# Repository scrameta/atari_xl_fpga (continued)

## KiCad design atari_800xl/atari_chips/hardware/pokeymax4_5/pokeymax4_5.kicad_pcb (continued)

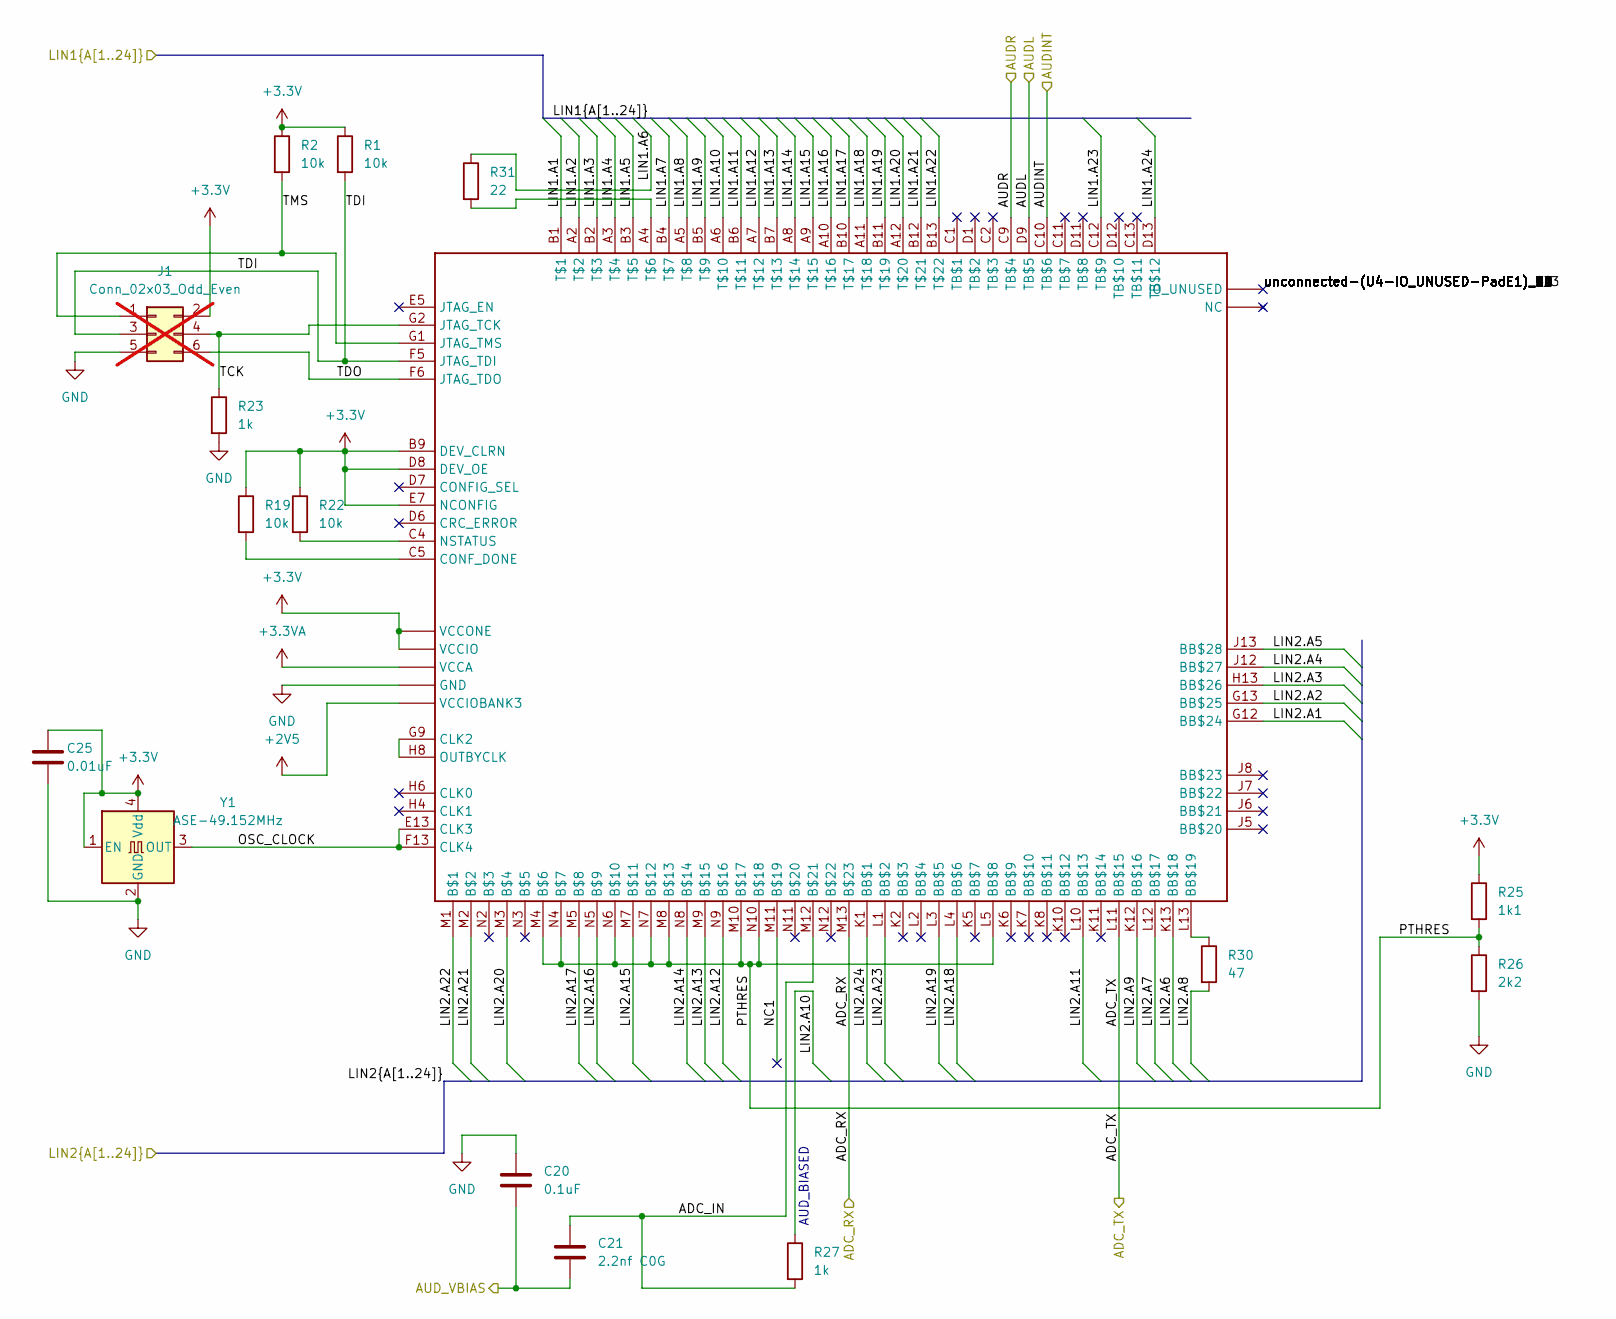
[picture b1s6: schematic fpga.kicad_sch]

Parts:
C20: 0.1uF; C_0402_1005Metric; LCSC C1525
C21: 2.2nf C0G; C_0402_1005Metric; LCSC C2987940
C25: 0.01uF; C_0603_1608Metric; LCSC C57112
J1: Conn_02x03_Odd_Even; PinHeader_2x03_P2.54mm_Vertical; not fitted
R1, R2, R19, R22: 10k; R_0603_1608Metric; LCSC C25804
R23: 1k; R_0603_1608Metric; LCSC C21190
R25: 1k1; R_0603_1608Metric; LCSC C705736
R26: 2k2; R_0603_1608Metric; LCSC C4190
R27: 1k; R_0402_1005Metric; LCSC C11702
R30: 47; R_0402_1005Metric; LCSC C137973
R31: 22; R_0402_1005Metric; LCSC C25092
U4: U169SMALL; LCSC C1551099
Y1: ASE-49.152MHz; Oscillator_SMD_Abracon_ASE-4Pin_3.2x2.5mm; LCSC C2901591

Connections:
+2V5: U4.L6 (VCCIOBANK3), U4.L7 (VCCIOBANK3), U4.L8 (VCCIOBANK3); also elsewhere on the board
+3.3V: C25.1, J1.2, R1.1, R2.1, R19.1, R22.1, R25.1, U4.B9 (DEV_CLRN), U4.C6 (VCCIO), U4.C7 (VCCIO), U4.C8 (VCCIO), U4.D8 (DEV_OE), U4.E7 (NCONFIG), U4.F2 (VCCIO), U4.F7 (VCCONE), U4.F11 (VCCIO), U4.G3 (VCCIO), U4.G6 (VCCONE), U4.G8 (VCCONE), U4.G11 (VCCIO), U4.H7 (VCCONE), U4.H11 (VCCIO), U4.J3 (VCCIO), U4.J11 (VCCIO), U4.K3 (VCCIO), Y1.1 (EN), Y1.4 (Vdd); also elsewhere on the board
+3.3VA: U4.D4 (VCCA), U4.D10 (VCCA), U4.K4 (VCCA), U4.K9 (VCCA); also elsewhere on the board
/ADC/ADC_RX: U4.M13; also elsewhere on the board
/ADC/ADC_TX: U4.L11 (BB$15); also elsewhere on the board
/ADC/AUD_VBIAS: C20.2, C21.2; also elsewhere on the board
/Audio output/AUDINT: U4.C10 (TB$6); also elsewhere on the board
/Audio output/AUDL: U4.D9 (TB$5); also elsewhere on the board
/Audio output/AUDR: U4.C9 (TB$4); also elsewhere on the board
/FPGA/ADC_IN: C21.1, R27.2, U4.M12
/FPGA/LIN1.A1: U4.B1; also elsewhere on the board
/FPGA/LIN1.A2: U4.A2; also elsewhere on the board
/FPGA/LIN1.A3: U4.B2; also elsewhere on the board
/FPGA/LIN1.A4: U4.A3; also elsewhere on the board
/FPGA/LIN1.A5: U4.B3; also elsewhere on the board
/FPGA/LIN1.A6: R31.1; also elsewhere on the board
/FPGA/LIN1.A7: U4.B4; also elsewhere on the board
/FPGA/LIN1.A8: U4.A5; also elsewhere on the board
/FPGA/LIN1.A9: U4.B5; also elsewhere on the board
/FPGA/LIN1.A10: U4.A6; also elsewhere on the board
/FPGA/LIN1.A11: U4.B6; also elsewhere on the board
/FPGA/LIN1.A12: U4.A7; also elsewhere on the board
/FPGA/LIN1.A13: U4.B7; also elsewhere on the board
/FPGA/LIN1.A14: U4.A8; also elsewhere on the board
/FPGA/LIN1.A15: U4.A9; also elsewhere on the board
/FPGA/LIN1.A16: U4.A10; also elsewhere on the board
/FPGA/LIN1.A17: U4.B10; also elsewhere on the board
/FPGA/LIN1.A18: U4.A11; also elsewhere on the board
/FPGA/LIN1.A19: U4.B11; also elsewhere on the board
/FPGA/LIN1.A20: U4.A12; also elsewhere on the board
/FPGA/LIN1.A21: U4.B12; also elsewhere on the board
/FPGA/LIN1.A22: U4.B13; also elsewhere on the board
/FPGA/LIN1.A23: U4.C12 (TB$9); also elsewhere on the board
/FPGA/LIN1.A24: U4.D13 (TB$12); also elsewhere on the board
/FPGA/LIN2.A1: U4.G12 (BB$24); also elsewhere on the board
/FPGA/LIN2.A2: U4.G13 (BB$25); also elsewhere on the board
/FPGA/LIN2.A3: U4.H13 (BB$26); also elsewhere on the board
/FPGA/LIN2.A4: U4.J12 (BB$27); also elsewhere on the board
/FPGA/LIN2.A5: U4.J13 (BB$28); also elsewhere on the board
/FPGA/LIN2.A6: U4.K13 (BB$18); also elsewhere on the board
/FPGA/LIN2.A7: U4.L12 (BB$17); also elsewhere on the board
/FPGA/LIN2.A8: R30.2; also elsewhere on the board
/FPGA/LIN2.A9: U4.K12 (BB$16); also elsewhere on the board
/FPGA/LIN2.A10: R27.1; also elsewhere on the board
/FPGA/LIN2.A11: U4.L10 (BB$13); also elsewhere on the board
/FPGA/LIN2.A12: U4.N9; also elsewhere on the board
/FPGA/LIN2.A13: U4.M9; also elsewhere on the board
/FPGA/LIN2.A14: U4.N8; also elsewhere on the board
/FPGA/LIN2.A15: U4.M7; also elsewhere on the board
/FPGA/LIN2.A16: U4.N5; also elsewhere on the board
/FPGA/LIN2.A17: U4.M5; also elsewhere on the board
/FPGA/LIN2.A18: U4.L4 (BB$6); also elsewhere on the board
/FPGA/LIN2.A19: U4.L3 (BB$5); also elsewhere on the board
/FPGA/LIN2.A20: U4.M3; also elsewhere on the board
/FPGA/LIN2.A21: U4.M2; also elsewhere on the board
/FPGA/LIN2.A22: U4.M1; also elsewhere on the board
/FPGA/LIN2.A23: U4.L1 (BB$2); also elsewhere on the board
/FPGA/LIN2.A24: U4.K1 (BB$1); also elsewhere on the board
/FPGA/NC1: U4.M11
/FPGA/OSC_CLOCK: U4.E13 (CLK3), U4.F13 (CLK4), Y1.3 (OUT)
/FPGA/PTHRES: R25.2, R26.1, U4.L5 (BB$8), U4.M4, U4.M8, U4.M10, U4.N4, U4.N6, U4.N7, U4.N10
/FPGA/TCK: J1.4, R23.1, U4.G2 (JTAG_TCK)
/FPGA/TDI: J1.3, R1.2, U4.F5 (JTAG_TDI)
/FPGA/TDO: J1.6, U4.F6 (JTAG_TDO)
/FPGA/TMS: J1.1, R2.2, U4.G1 (JTAG_TMS)
GND: C20.1, C25.2, J1.5, R23.2, R26.2, U4.A1 (GND), U4.A13 (GND), U4.B8 (GND), U4.C3 (GND), U4.D5 (GND), U4.E11 (GND), U4.F3 (GND), U4.G7 (GND), U4.H12 (GND), U4.J4 (GND), U4.L9 (GND), U4.M6 (GND), U4.N1 (GND), U4.N13 (GND), Y1.2 (GND); also elsewhere on the board
unnamed: R30.1, U4.L13 (BB$19)
unnamed: U4.G9 (CLK2), U4.H8 (OUTBYCLK)
unnamed: R19.2, U4.C5 (CONF_DONE)
unnamed: R22.2, U4.C4 (NSTATUS)
unnamed: R31.2, U4.A4

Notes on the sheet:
AUD_BIASED

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
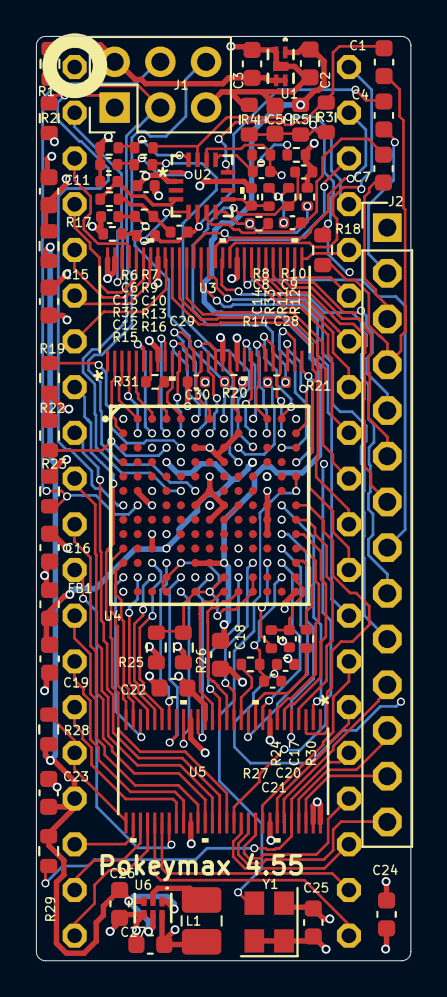
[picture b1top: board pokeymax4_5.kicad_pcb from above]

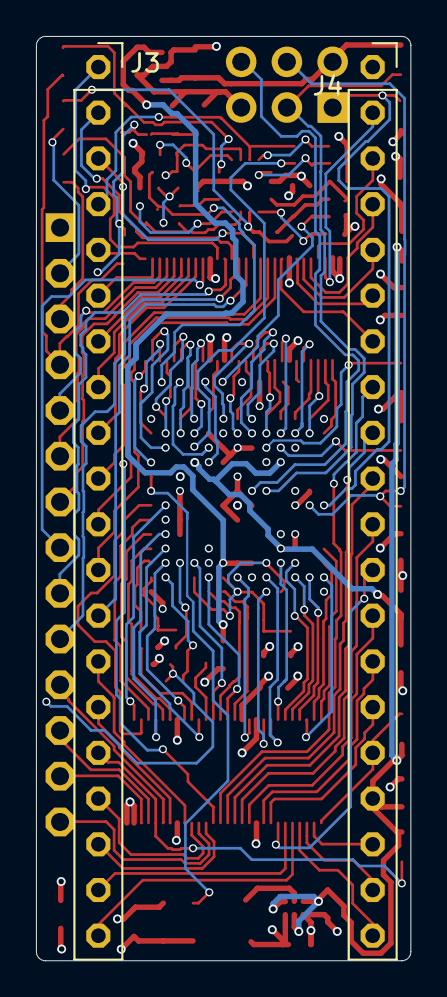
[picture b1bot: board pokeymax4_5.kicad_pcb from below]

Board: 4 copper layers, 20.8 x 51.3 mm, 76 parts (2 on the bottom side), 139 nets.

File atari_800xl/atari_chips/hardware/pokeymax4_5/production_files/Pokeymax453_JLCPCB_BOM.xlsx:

Designator | Footprint | JLCPCB Part #（optional） | Comment | Description | Mfgr part
C10,C20 | C_0402_1005Metric | C1525 | CAP CER 0.1UF 16V X7R 0402 | 100nF 16V X7R ±10% 0402 Multilayer Ceramic Capacitors MLCC - SMD/SMT ROHS | CL05B104KO5NNNC
R11,R9,R13 | R_0402_1005Metric | C278600 | RES SMD 560 OHM 1% 1/10W 0402 | -55℃~+155℃ 100mW 560Ω Thick Film Resistor ±1% ±100ppm/℃ 0402 Chip Resistor - Su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 | ERJ2RKF5600X
R18 | R_0603_1608Metric | C123420 | RES 220K OHM 1% 0603 | -55℃~+155℃ 100mW 220kΩ 75V Thick Film Resistor ±1% ±100ppm/℃ 0603 Chip Resistor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 | RC0603FR-07220KL
L1 | L_1008_2520Metric_Pad1.43x2.20mm_HandSolder | C171753 | FIXED IND 1UH 1.5A 113 MOHM SMD | 1.5A 112.5mΩ 1uH 70MHz ±20% 1008 Inductors (SMD) ROHS | LQM2HPN1R0MJ0L
R21,R20 | R_0402_1005Metric | C138002 | RES 33 OHM 1% 0402 | -55℃~+155℃ 33Ω 50V 62.5mW Thick Film Resistor ±1% ±100ppm/℃ 0402 Chip Resistor 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 | RC0402FR-0733RL
C7,C1,C4,C26 | C_0603_1608Metric | C415535 | CAP CER 2.2UF 25V X7R 0603 audio | 2.2uF 25V X7R ±10% 0603 Multilayer Ceramic Capacitors MLCC - SMD/SMT ROHS | GRM188Z71E225KE43D
C27 | C_0603_1608Metric | C1705 | CAP CER 4.7UF 10V X5R 0603 | 10V 4.7uF X5R ±10% 0603 Multilayer Ceramic Capacitors MLCC - SMD/SMT ROHS | CL10A475KP8NNNC
C24,C22,C18,C15,C3,C19,C2,C16,C23 | C_0603_1608Metric | C108079 | CAP CER 0.1UF 16V X7R 0603 | 100nF 16V X7R ±10% 0603 Multilayer Ceramic Capacitors MLCC - SMD/SMT ROHS | CC0603KRX7R7BB104
U2 | QFN16_3X3_STM | C2058240 | IC OPAMP GP 4 CIRCUIT 16QFN | -40℃~+125℃ 1.3MHz 120uA 1uV/℃ 2.3V~5.5V 20nV/√Hz@10kHz 21mA 27nA 4 4mV 5.5V 500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 | TSV854IQ4T
C11 | C_0603_1608Metric | C2762594 | CAP CER 22uF 16V 0603 | 16V 22uF X5R ±20% 0603 Multilayer Ceramic Capacitors MLCC - SMD/SMT ROHS | CL10A226MO7JZNC
R12,R15,R6 | R_0402_1005Metric | C490819 | RES SMD 20K OHM 0.1% 1/16W 0402 | -55℃~+155℃ 20kΩ 50V 63mW Thin Film Resistor ±0.1% ±25ppm/℃ 0402 Chip Resistor -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 | ERA2AEB203X
R26 | R_0603_1608Metric | C114662 | RES 2.2K OHM 1% 1/10W 0603 | -55℃~+155℃ 100mW 2.2kΩ 75V Thick Film Resistor ±1% ±100ppm/℃ 0603 Chip Resistor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 | RC0603FR-072K2L
Y1 | Oscillator_SMD_Abracon_ASE-4Pin_3.2x2.5mm | C2901591 | RES 2.2K OHM 1% 1/10W 0603 | -40℃~+85℃ 1.62V~3.63V 20mA 49.152MHz CMOS ±20ppm ±30ppm SMD3225-4P Crystal Osci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 | SX3M49.152M20F30TNN
FB1 | L_0603_1608Metric | C710367 | FERRITE BEAD 600 OHM 0603 1LN | -55℃~+125℃ 1 350mΩ 500mA 600Ω@100MHz ±25% 0603 Ferrite Beads ROHS | BLM18EG601SZ1D
C14,C13,C8 | C_0402_1005Metric | C882581 | CAP CER 220pF C0G 0402 | 220pF 50V C0G ±1% 0402 Multilayer Ceramic Capacitors MLCC - SMD/SMT ROHS | GCM1555C1H221FA16D
U5,U3 | DGV56-L | C2674751 | IC BUS SWITCH 12 X 1:1 56-TVSOP | -40℃~+85℃ 0.25ns@3.3V,50pF 2.3V~3.6V 24/24 70uA Single Supply TVSOP-56 Signal S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 | SN74CB3T16211DGVR
C17 | C_0402_1005Metric | C161523 | CAP CER 1000PF 50V C0G/NP0 0403 | 1nF 50V C0G ±1% 0402 Multilayer Ceramic Capacitors MLCC - SMD/SMT ROHS | GRM1555C1H102FA01D
R5 | R_0603_1608Metric | C25805 | RES 110K OHM 1% 1/10W 0603 | -55℃~+155℃ 100mW 110kΩ 75V Thick Film Resistor ±1% ±100ppm/℃ 0603 Chip Resistor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 | 0603WAF1103T5E
R1,R2,R22,R19,R4 | R_0603_1608Metric | C130232 | RES 10K OHM 1% 1/10W 0603 | -55℃~+155℃ 100mW 10kΩ 75V Thick Film Resistor ±1% ±100ppm/℃ 0603 Chip Resistor 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 | RK73H1JTTD1002F
R17 | R_0603_1608Metric | C109318 | RES 10 OHM 1% 1/10W 0603 | -55℃~+155℃ 100mW 10Ω 75V Thick Film Resistor ±1% ±200ppm/℃ 0603 Chip Resistor -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 | RC0603FR-0710RL
R24 | R_0402_1005Metric | C138041 | RES 1k1 OHM 1% 0402 | -55℃~+155℃ 1.1kΩ 50V 62.5mW Thick Film Resistor ±1% ±100ppm/℃ 0402 Chip Resisto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 | RC0402FR-071K1L
C9,C6,C12 | C_0402_1005Metric | C576740 | CAP 18nF 0402 audio | 18nF 50V X7R ±10% 0402 Multilayer Ceramic Capacitors MLCC - SMD/SMT ROHS | CC0402KRX7R9BB183
U1 | TDFN4_1P2X1P6_MCH | C622555 | IC REG LINEAR 2.5V 200MA 4-TMLF | -40℃~+125℃@(Tj) 1 2.5V 200mA 3.6V 85dB@(100Hz) Fixed Over Current Protection Po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 | MIC94310-JYMT-TR
R14,R7,R16,R10 | R_0402_1005Metric | C25744 | RES SMD 10K OHM 0.1% 1/16W 0402 | -55℃~+155℃ 10kΩ 50V 62.5mW Thick Film Resistor ±1% ±100ppm/℃ 0402 Chip Resistor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 | 0402WGF1002TCE
R3 | R_0603_1608Metric | C105579 | RES 47K OHM 0603 | -55℃~+155℃ 100mW 47kΩ 75V Thick Film Resistor ±1% ±100ppm/℃ 0603 Chip Resistor 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 | RC0603FR-0747KL
R8 | R_0402_1005Metric | C166559 | RES 50K OHM 1% 1/16W 0402 | -55℃~+155℃ 50V 50kΩ 62.5mW Thick Film Resistor ±1% ±100ppm/℃ 0402 Chip Resistor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 | RTT025002FTH
U6 | DRY6 | C398923 | IC REG BUCK 3.3V 500MA 6SON | -40℃~+125℃@(TJ) 1 2.05V~6V 22uA 2MHz 3.3V 500mA Buck Buck Built-In Fixed Yes SO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 | TPS62237DRYR
C21 | C_0402_1005Metric | C2987940 | CAP 2.2nF 0402 C0G | 2.2nF 50V C0G ±2% 0402 Multilayer Ceramic Capacitors MLCC - SMD/SMT ROHS | GRM1555C1H222GA01D
C5 | C_0603_1608Metric | C2959727 | CAP CER 10UF 10V X7R 0603 | 10V 10uF X7R ±10% 0603 Multilayer Ceramic Capacitors MLCC - SMD/SMT ROHS | GRM188Z71A106KA73D
R23 | R_0603_1608Metric | C2484712 | RES 1K OHM 1% 1/10W 0603 | -55℃~+155℃ 100mW 1kΩ 75V Thick Film Resistor ±1% ±100ppm/℃ 0603 Chip Resistor -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 | RMCF0603FT1K00
C25 | C_0603_1608Metric | C1589 | CAP CER 10000PF 50V X7R 0603 | 10nF 50V X7R ±10% 0603 Multilayer Ceramic Capacitors MLCC - SMD/SMT ROHS | CL10B103KB8NNNC
U4 | U169SMALL | C1551099 | IC FPGA 130 I/O 169UBGA | -40℃~+100℃ 1000 16000 562176bit UBGA-169 Programmable Logic Device (CPLDs/FPGAs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 | 10M16SCU169I7G
R25 | R_0603_1608Metric | C22764 | RES 1.1K OHM 1% 1/10W 0603 | -55℃~+155℃ 1.1kΩ 100mW 75V Thick Film Resistor ±1% ±100ppm/℃ 0603 Chip Resistor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 | 0603WAF1101T5E
R27 | R_0402_1005Metric | C106235 | RES 1K OHM 1% 0402 | -55℃~+155℃ 1kΩ 50V 62.5mW Thick Film Resistor ±1% ±100ppm/℃ 0402 Chip Resistor 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 | RC0402FR-071KL
R30 | R_0402_1005Metric | C25118 | RES 47 OHM 1% 0402 | -55℃~+155℃ 47Ω 50V 62.5mW Thick Film Resistor ±1% ±100ppm/℃ 0402 Chip Resistor 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 | 0402WGF470JTCE
R31 | R_0402_1005Metric | C25092 | RES 22 OHM 1% 0402 | -55℃~+155℃ 22Ω 50V 62.5mW Thick Film Resistor ±1% ±100ppm/℃ 0402 Chip Resistor 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 | 0402WGF220JTCE

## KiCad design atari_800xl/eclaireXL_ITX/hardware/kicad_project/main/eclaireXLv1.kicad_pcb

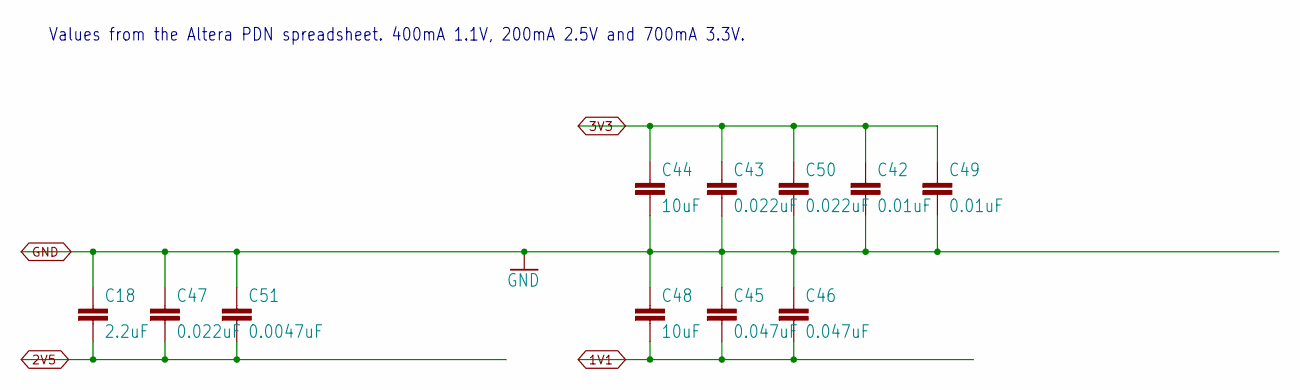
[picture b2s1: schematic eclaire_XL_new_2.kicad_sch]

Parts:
C18: 2.2uF; C0805
C42, C49: 0.01uF; C0805
C43, C47, C50: 0.022uF; C0805
C44, C48: 10uF; C0805
C45, C46: 0.047uF; C0805
C51: 0.0047uF; C0805

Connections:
1V1: C45.2, C46.2, C48.2; also elsewhere on the board
2V5: C18.2, C47.2, C51.2; also elsewhere on the board
3V3: C42.1, C43.1, C44.1, C49.1, C50.1; also elsewhere on the board

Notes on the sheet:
Values from the Altera PDN spreadsheet. 400mA 1.1V, 200mA 2.5V and 700mA 3.3V.

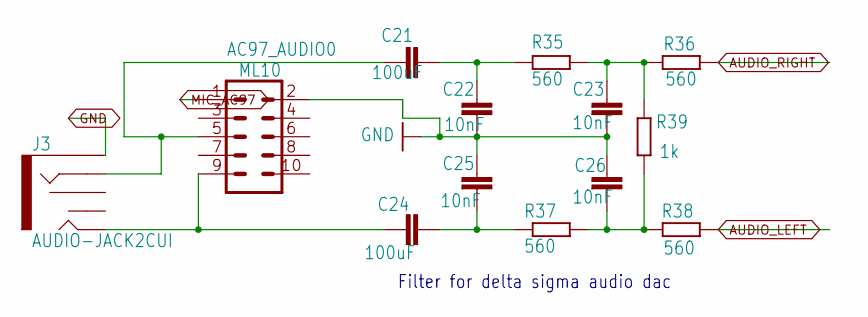
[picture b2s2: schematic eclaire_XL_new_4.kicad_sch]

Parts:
AC97_AUDIO0: ML10
C21, C24: 100uF; C1206
C22, C23, C25, C26: 10nF; C0805
J3: AUDIO-JACK2CUI; AUDIO-JACK-CUI-353X
R35, R36, R37, R38: 560; M0805
R39: 1k; M0805

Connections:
AUDIO_LEFT: R38.2; also elsewhere on the board
AUDIO_RIGHT: R36.2; also elsewhere on the board
MIC_AC97: AC97_AUDIO0.1; also elsewhere on the board
unnamed: C21.2, C22.1, R35.1
unnamed: C23.1, R35.2, R36.1, R39.2
unnamed: C26.2, R37.2, R38.1, R39.1
unnamed: AC97_AUDIO0.9, C24.1, J3.P$2 (TIP)
unnamed: AC97_AUDIO0.5, C21.1, J3.P$3 (RING)
unnamed: C24.2, C25.2, R37.1

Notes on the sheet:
Filter for delta sigma audio dac

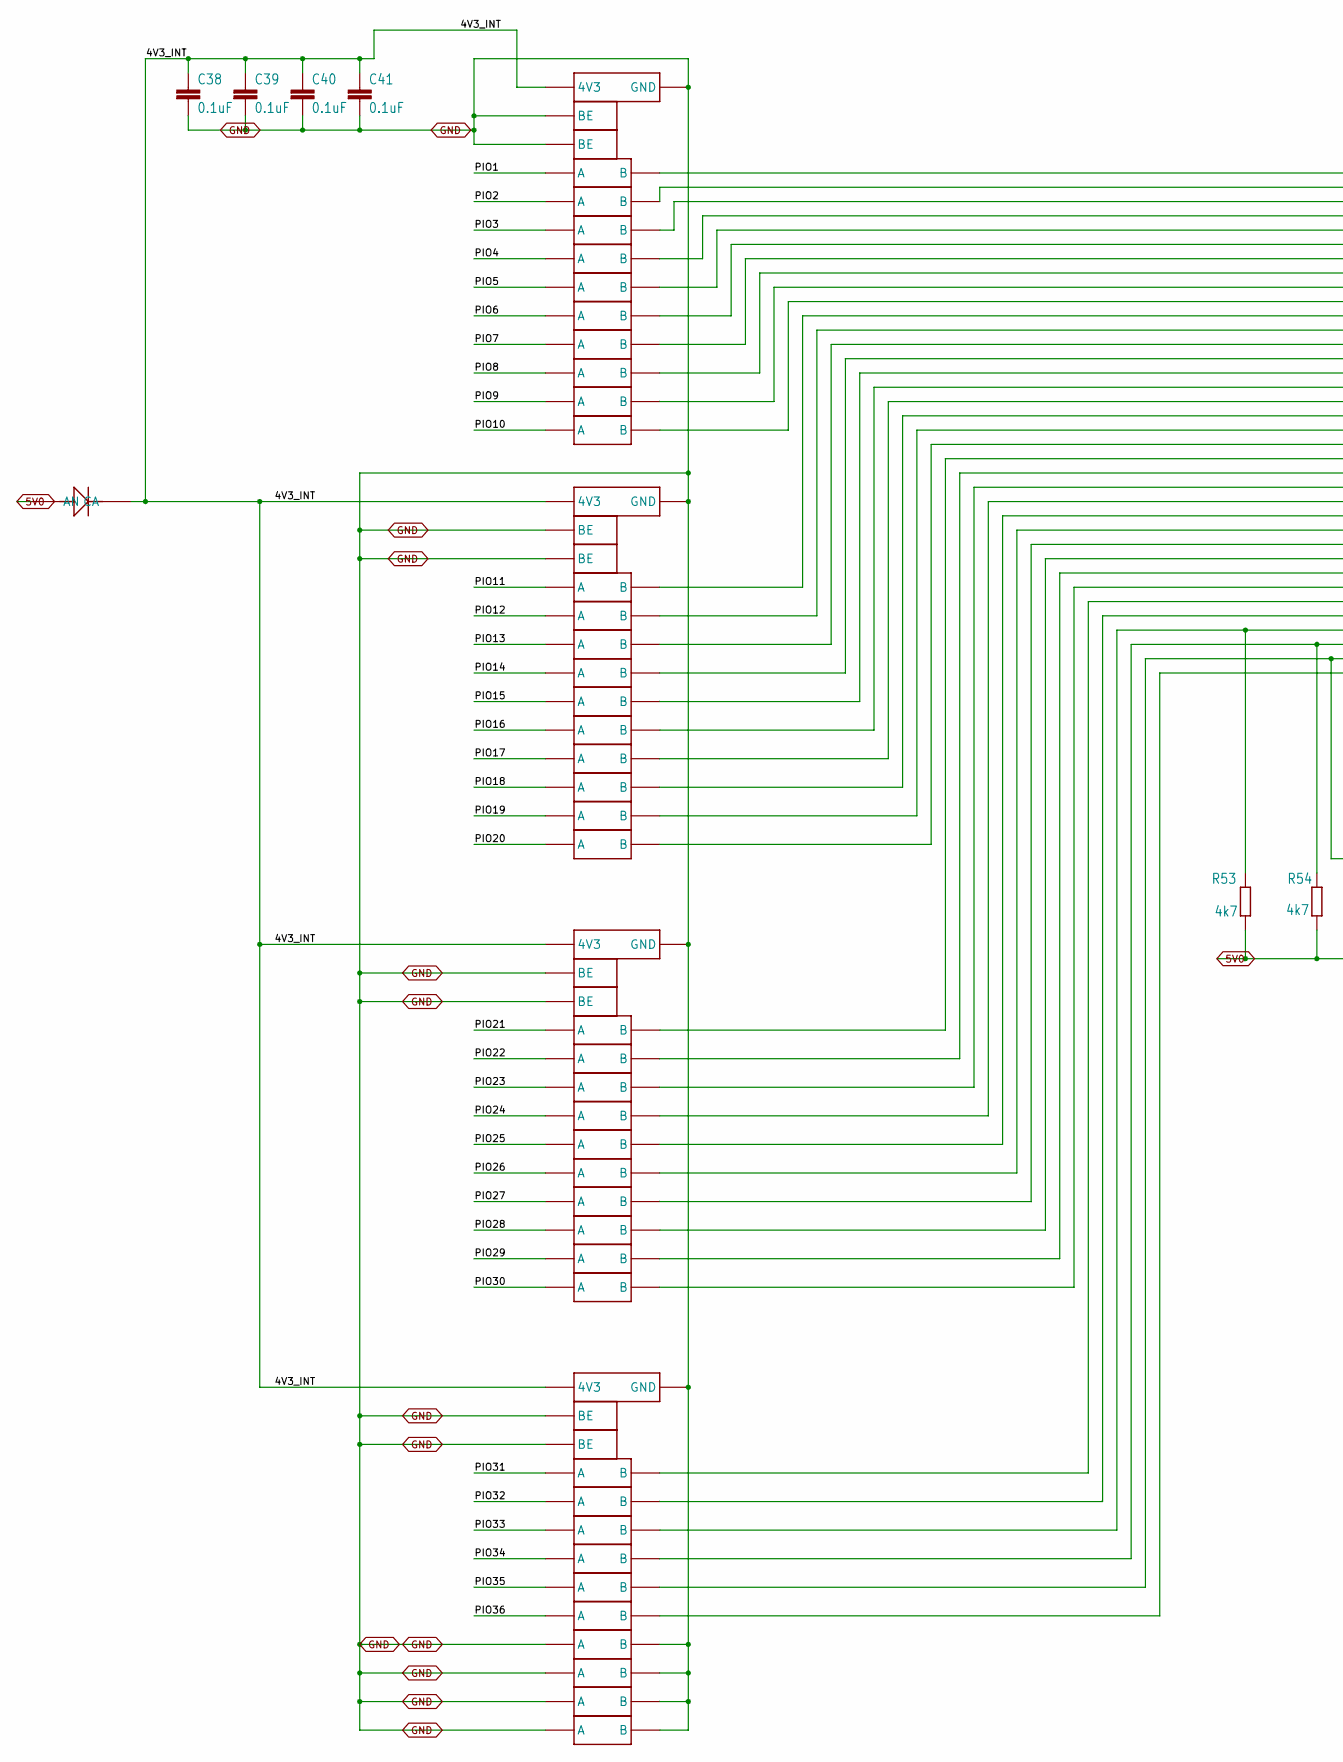
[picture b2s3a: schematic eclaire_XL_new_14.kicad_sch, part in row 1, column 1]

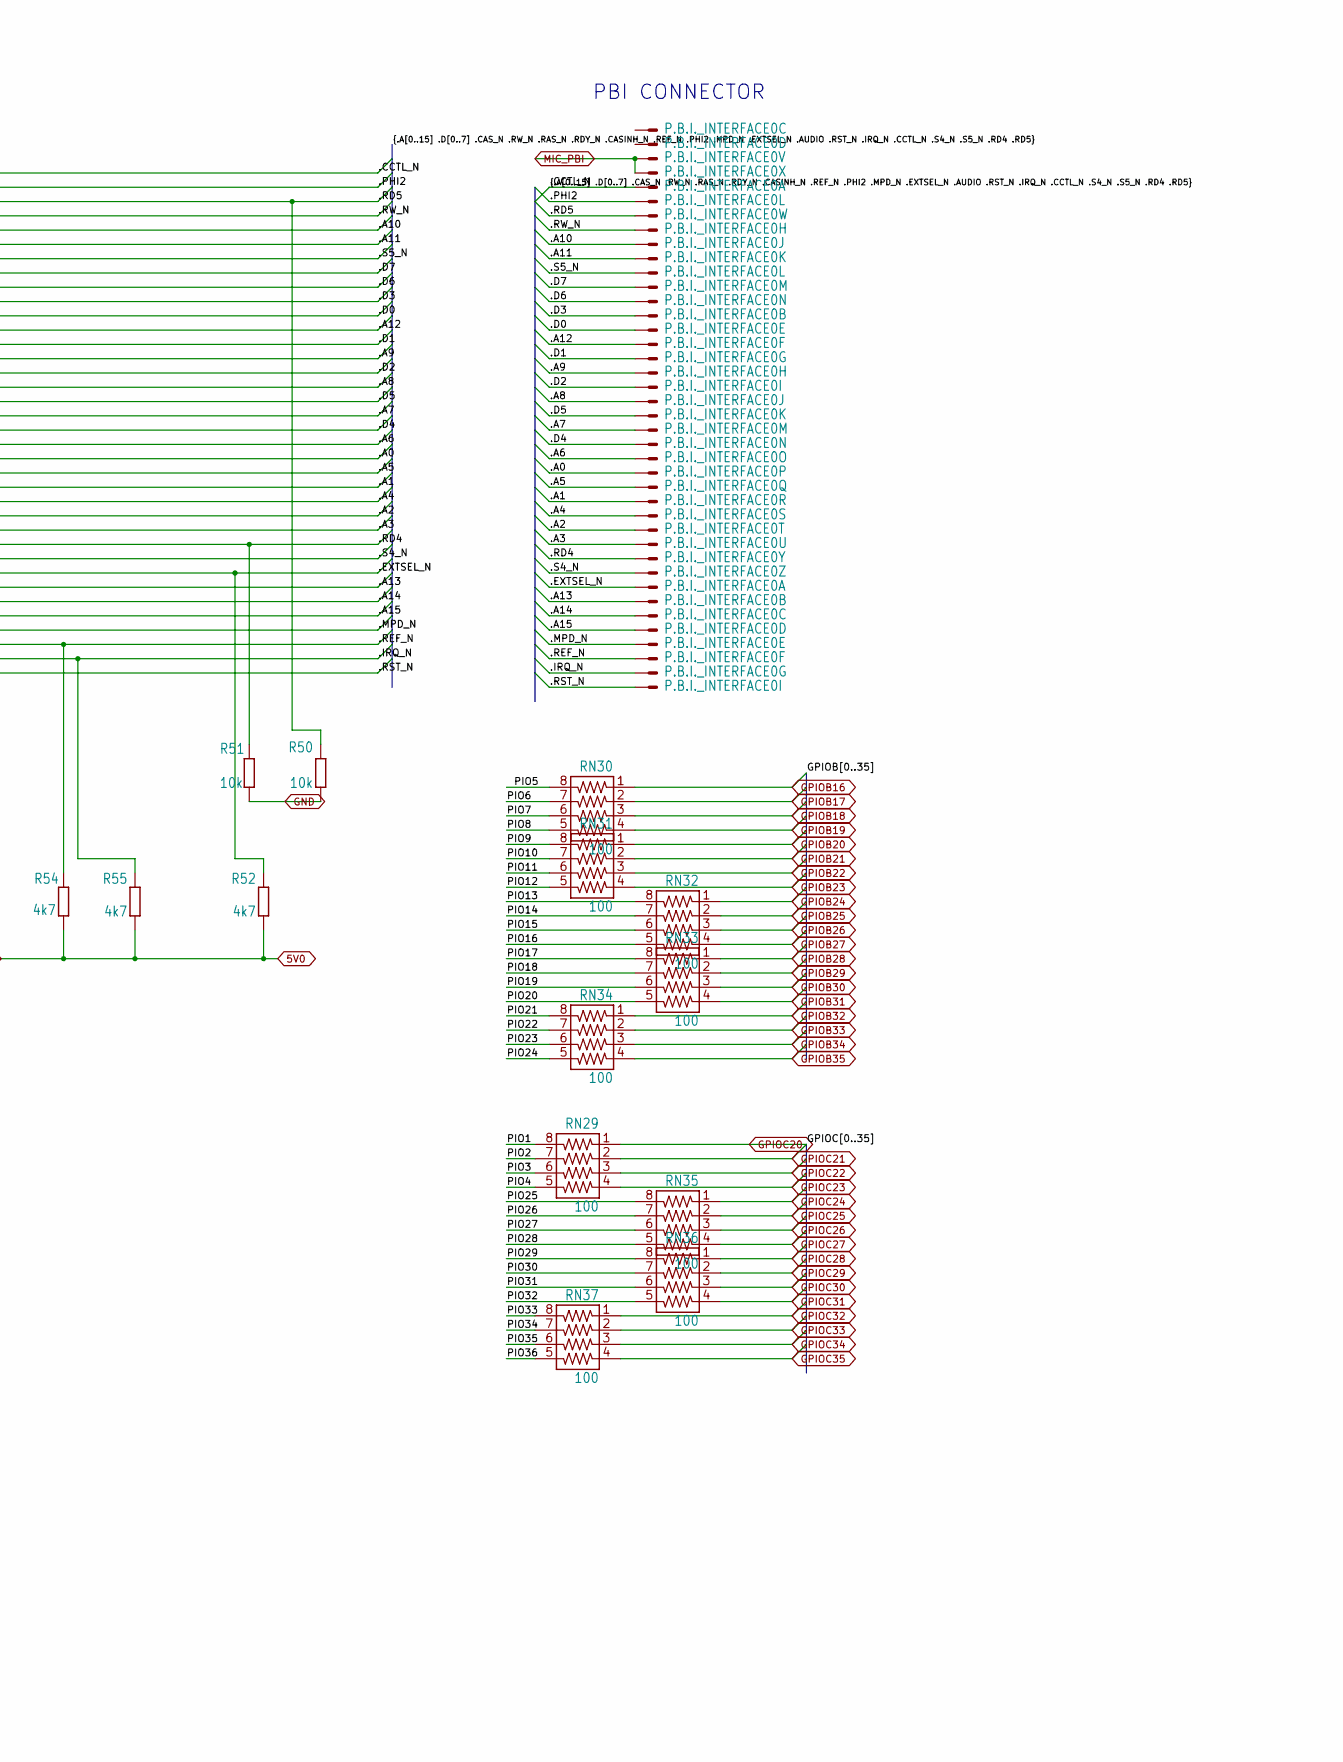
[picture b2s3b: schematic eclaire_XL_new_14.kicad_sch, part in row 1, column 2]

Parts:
C38, C39, C40, C41: 0.1uF; C0805K
D3: 1N4148; SOD123
IC1: U14; TSSOP24
IC2: U15; TSSOP24
IC3: U16; TSSOP24
IC4: U17; TSSOP24
P.B.I._INTERFACE0: ML40E; ML40
R50, R51: 10k; M0805
R52, R53, R54, R55: 4k7; M0805
RN29, RN30, RN31, RN32, RN33, RN34, RN35, RN36, RN37: 100; 743-8

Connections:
4V3_INT: C38.1, C39.1, C40.1, C41.1, D3.1 (CA), IC1.24 (4V3), IC2.24 (4V3), IC3.24 (4V3), IC4.24 (4V3)
5V0: D3.2 (AN), R52.1, R53.1, R54.1, R55.1; also elsewhere on the board
.A0: IC3.2 (B), P.B.I._INTERFACE0.23
.A1: IC3.6 (B), P.B.I._INTERFACE0.25
.A2: IC3.10 (B), P.B.I._INTERFACE0.27
.A3: IC3.15 (B), P.B.I._INTERFACE0.28
.A4: IC3.9 (B), P.B.I._INTERFACE0.26
.A5: IC3.5 (B), P.B.I._INTERFACE0.24
.A6: IC2.23 (B), P.B.I._INTERFACE0.22
.A7: IC2.19 (B), P.B.I._INTERFACE0.20
.A8: IC2.15 (B), P.B.I._INTERFACE0.18
.A9: IC2.9 (B), P.B.I._INTERFACE0.16
.A10: IC1.10 (B), P.B.I._INTERFACE0.5
.A11: IC1.15 (B), P.B.I._INTERFACE0.6
.A12: IC2.5 (B), P.B.I._INTERFACE0.14
.A13: IC3.23 (B), P.B.I._INTERFACE0.34
.A14: IC4.2 (B), P.B.I._INTERFACE0.35
.A15: IC4.5 (B), P.B.I._INTERFACE0.36
.CCTL_N: IC1.2 (B), P.B.I._INTERFACE0.1
.D0: IC2.2 (B), P.B.I._INTERFACE0.13
.D1: IC2.6 (B), P.B.I._INTERFACE0.15
.D2: IC2.10 (B), P.B.I._INTERFACE0.17
.D3: IC1.23 (B), P.B.I._INTERFACE0.10
.D4: IC2.20 (B), P.B.I._INTERFACE0.21
.D5: IC2.16 (B), P.B.I._INTERFACE0.19
.D6: IC1.20 (B), P.B.I._INTERFACE0.9
.D7: IC1.19 (B), P.B.I._INTERFACE0.8
.EXTSEL_N: IC3.20 (B), P.B.I._INTERFACE0.33, R52.2
.IRQ_N: IC4.10 (B), P.B.I._INTERFACE0.39, R55.2
.MPD_N: IC4.6 (B), P.B.I._INTERFACE0.37, R53.2
.PHI2: IC1.5 (B), P.B.I._INTERFACE0.2
.RD4: IC3.16 (B), P.B.I._INTERFACE0.31, R51.2
.RD5: IC1.6 (B), P.B.I._INTERFACE0.3, R50.2
.REF_N: IC4.9 (B), P.B.I._INTERFACE0.38, R54.2
.RST_N: IC4.15 (B), P.B.I._INTERFACE0.40
.RW_N: IC1.9 (B), P.B.I._INTERFACE0.4
.S4_N: IC3.19 (B), P.B.I._INTERFACE0.32
.S5_N: IC1.16 (B), P.B.I._INTERFACE0.7
GPIOB16: RN30.1; also elsewhere on the board
GPIOB17: RN30.2; also elsewhere on the board
GPIOB18: RN30.3; also elsewhere on the board
GPIOB19: RN30.4; also elsewhere on the board
GPIOB20: RN31.1; also elsewhere on the board
GPIOB21: RN31.2; also elsewhere on the board
GPIOB22: RN31.3; also elsewhere on the board
GPIOB23: RN31.4; also elsewhere on the board
GPIOB24: RN32.1; also elsewhere on the board
GPIOB25: RN32.2; also elsewhere on the board
GPIOB26: RN32.3; also elsewhere on the board
GPIOB27: RN32.4; also elsewhere on the board
GPIOB28: RN33.1; also elsewhere on the board
GPIOB29: RN33.2; also elsewhere on the board
GPIOB30: RN33.3; also elsewhere on the board
GPIOB31: RN33.4; also elsewhere on the board
GPIOB32: RN34.1; also elsewhere on the board
GPIOB33: RN34.2; also elsewhere on the board
GPIOB34: RN34.3; also elsewhere on the board
GPIOB35: RN34.4; also elsewhere on the board
GPIOC20: RN29.1; also elsewhere on the board
GPIOC21: RN29.2; also elsewhere on the board
GPIOC22: RN29.3; also elsewhere on the board
GPIOC23: RN29.4; also elsewhere on the board
GPIOC24: RN35.1; also elsewhere on the board
GPIOC25: RN35.2; also elsewhere on the board
GPIOC26: RN35.3; also elsewhere on the board
GPIOC27: RN35.4; also elsewhere on the board
GPIOC28: RN36.1; also elsewhere on the board
GPIOC29: RN36.2; also elsewhere on the board
GPIOC30: RN36.3; also elsewhere on the board
GPIOC31: RN36.4; also elsewhere on the board
GPIOC32: RN37.1; also elsewhere on the board
GPIOC33: RN37.2; also elsewhere on the board
GPIOC34: RN37.3; also elsewhere on the board
MIC_PBI: P.B.I._INTERFACE0.29, P.B.I._INTERFACE0.30; also elsewhere on the board
PIO1: IC1.3 (A), RN29.8
PIO2: IC1.4 (A), RN29.7
PIO3: IC1.7 (A), RN29.6
PIO4: IC1.8 (A), RN29.5
PIO5: IC1.11 (A), RN30.8
PIO6: IC1.14 (A), RN30.7
PIO7: IC1.17 (A), RN30.6
PIO8: IC1.18 (A), RN30.5
PIO9: IC1.21 (A), RN31.8
PIO10: IC1.22 (A), RN31.7
PIO11: IC2.3 (A), RN31.6
PIO12: IC2.4 (A), RN31.5
PIO13: IC2.7 (A), RN32.8
PIO14: IC2.8 (A), RN32.7
PIO15: IC2.11 (A), RN32.6
PIO16: IC2.14 (A), RN32.5
PIO17: IC2.17 (A), RN33.8
PIO18: IC2.18 (A), RN33.7
PIO19: IC2.21 (A), RN33.6
PIO20: IC2.22 (A), RN33.5
PIO21: IC3.3 (A), RN34.8
PIO22: IC3.4 (A), RN34.7
PIO23: IC3.7 (A), RN34.6
PIO24: IC3.8 (A), RN34.5
PIO25: IC3.11 (A), RN35.8
PIO26: IC3.14 (A), RN35.7
PIO27: IC3.17 (A), RN35.6
PIO28: IC3.18 (A), RN35.5
PIO29: IC3.21 (A), RN36.8
PIO30: IC3.22 (A), RN36.7
PIO31: IC4.3 (A), RN36.6
PIO32: IC4.4 (A), RN36.5
PIO33: IC4.7 (A), RN37.8
PIO34: IC4.8 (A), RN37.7
PIO35: IC4.11 (A), RN37.6
PIO36: IC4.14 (A), RN37.5

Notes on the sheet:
PBI CONNECTOR

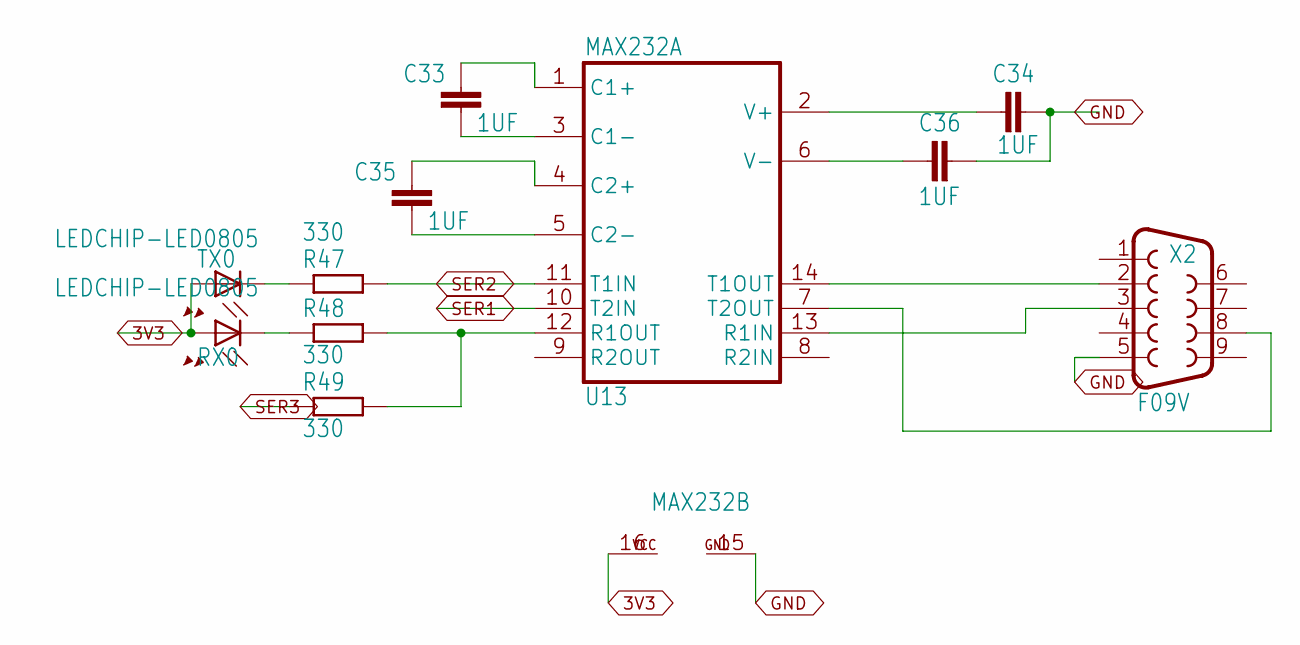
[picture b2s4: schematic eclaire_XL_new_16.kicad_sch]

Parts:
C33, C34, C35, C36: 1UF; C0805K
MAX232: U13; SO16L
R47, R48, R49: 330; M0805
RX0: LEDCHIP-LED0805; CHIP-LED0805
TX0: LEDCHIP-LED0805; CHIP-LED0805
X2: F09V

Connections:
3V3: MAX232.16 (VCC), RX0.A, TX0.A; also elsewhere on the board
unnamed: R47.1, TX0.C
unnamed: R48.1, RX0.C
unnamed: C34.1, MAX232.2 (V+)
unnamed: C33.2, MAX232.3 (C1-)
unnamed: C35.2, MAX232.5 (C2-)
unnamed: C33.1, MAX232.1 (C1+)
unnamed: C35.1, MAX232.4 (C2+)
unnamed: C36.1, MAX232.6 (V-)
unnamed: MAX232.14 (T1OUT), X2.2
unnamed: MAX232.13 (R1IN), X2.3
unnamed: MAX232.7 (T2OUT), X2.8
unnamed: MAX232.12 (R1OUT), R48.2, R49.2
SER1: MAX232.10 (T2IN); also elsewhere on the board
SER2: MAX232.11 (T1IN), R47.2; also elsewhere on the board
SER3: R49.1; also elsewhere on the board
